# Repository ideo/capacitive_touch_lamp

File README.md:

# Capacitive Touch Lamp
Eagle files and arduino code for the CHIDEO capacitive touch lamp. The surface is separated into nine capacitive touch surfaces. The eight outside surfaces control individual lights, while the center surface turns all lights on.

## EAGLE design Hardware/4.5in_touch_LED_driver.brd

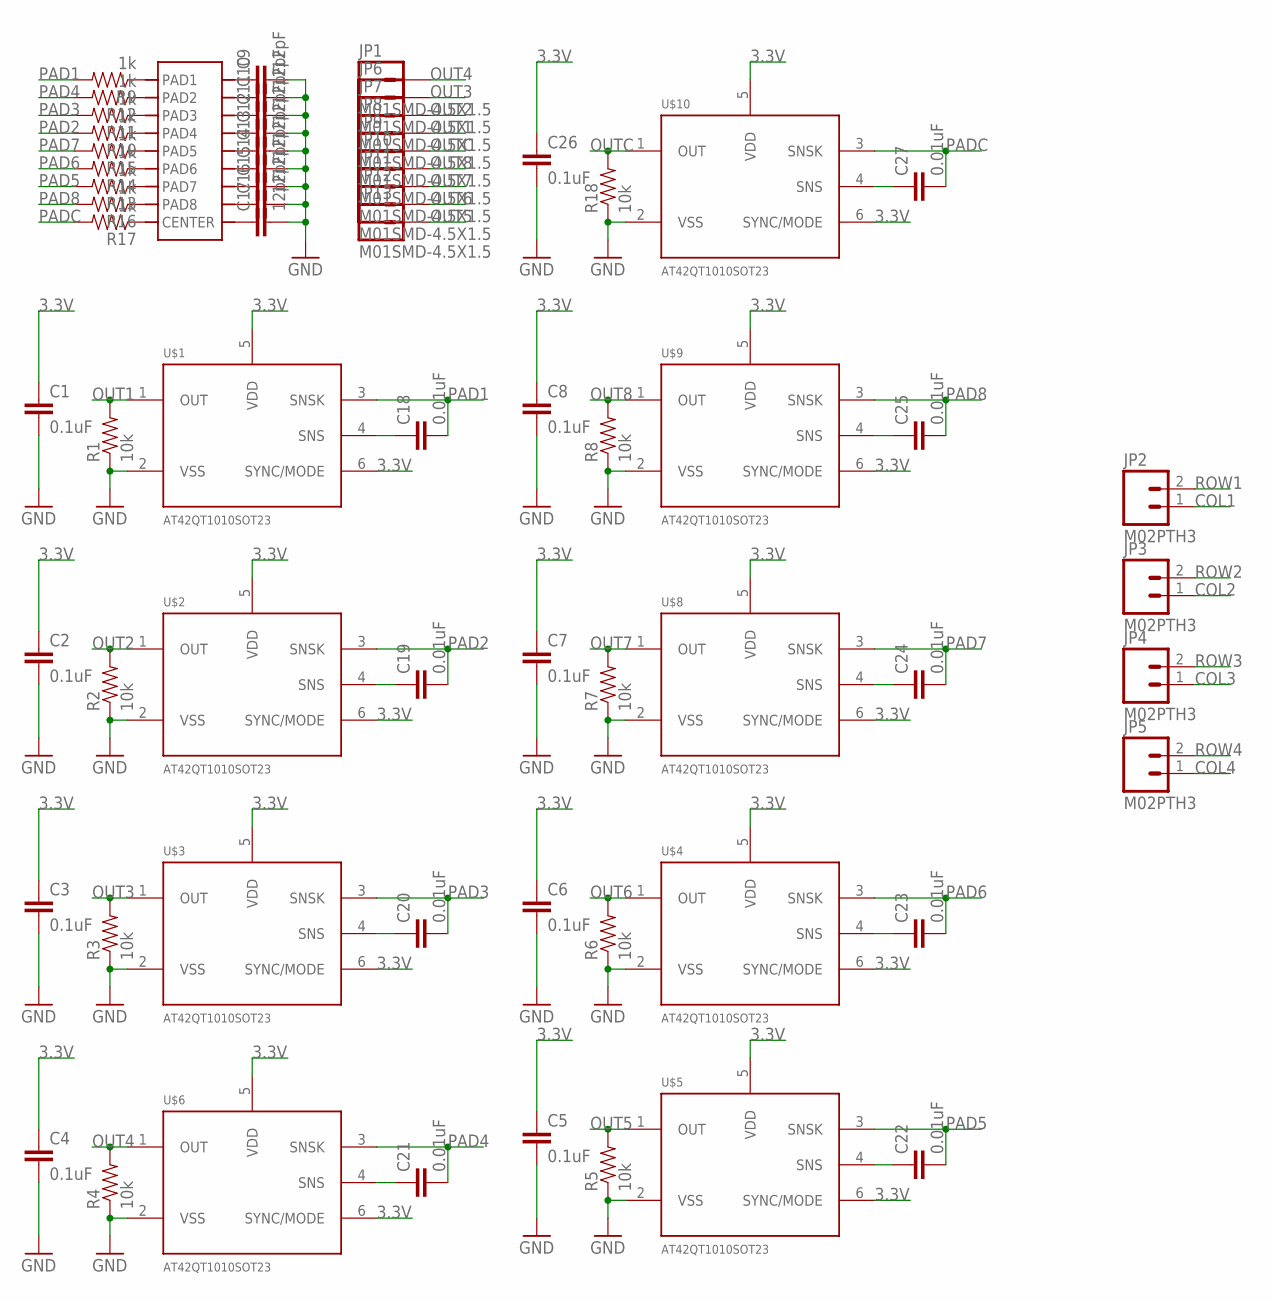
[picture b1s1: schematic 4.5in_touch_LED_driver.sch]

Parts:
C1, C2, C3, C4, C5, C6, C7, C8, C26: 0.1uF; 0603-CAP
C9, C10, C11, C12, C13, C14, C15, C16, C17: 12pF; 0805
C18, C19, C20, C21, C22, C23, C24, C25, C27: 0.01uF; 0805
JP1, JP6, JP7, JP8, JP9, JP10, JP11, JP12, JP13: M01SMD-4.5X1.5; PAD-1.5X4.5
JP2, JP3, JP4, JP5: M02PTH3; 1X02_LONGPADS
R1, R2, R3, R4, R5, R6, R7, R8, R18: 10k; 0603-RES
R9, R10, R11, R12, R13, R14, R15, R16, R17: 1k; 0603-RES
U$1, U$2, U$3, U$4, U$5, U$6, U$8, U$9, U$10: AT42QT1010SOT23; SOT23-6
U$7: 9_PAD_TOUCH4IN; 4IN_TOUCH_PAD

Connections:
3.3V: C1.1, C2.1, C3.1, C4.1, C5.1, C6.1, C7.1, C8.1, C26.1, U$1.5 (VDD), U$1.6 (SYNC/MODE), U$2.5 (VDD), U$2.6 (SYNC/MODE), U$3.5 (VDD), U$3.6 (SYNC/MODE), U$4.5 (VDD), U$4.6 (SYNC/MODE), U$5.5 (VDD), U$5.6 (SYNC/MODE), U$6.5 (VDD), U$6.6 (SYNC/MODE), U$8.5 (VDD), U$8.6 (SYNC/MODE), U$9.5 (VDD), U$9.6 (SYNC/MODE), U$10.5 (VDD), U$10.6 (SYNC/MODE)
COL1: JP2.1
COL2: JP3.1
COL3: JP4.1
COL4: JP5.1
GND: C1.2, C2.2, C3.2, C4.2, C5.2, C6.2, C7.2, C8.2, C9.2, C10.2, C11.2, C12.2, C13.2, C14.2, C15.2, C16.2, C17.2, C26.2, R1.1, R2.1, R3.1, R4.1, R5.1, R6.1, R7.1, R8.1, R18.1, U$1.2 (VSS), U$2.2 (VSS), U$3.2 (VSS), U$4.2 (VSS), U$5.2 (VSS), U$6.2 (VSS), U$8.2 (VSS), U$9.2 (VSS), U$10.2 (VSS)
unnamed: C9.1, U$7.P$10
unnamed: C10.1, U$7.P$11
unnamed: C11.1, U$7.P$12
unnamed: C12.1, U$7.P$13
unnamed: C13.1, U$7.P$14
unnamed: C14.1, U$7.P$15
unnamed: C15.1, U$7.P$16
unnamed: C16.1, U$7.P$17
unnamed: C17.1, U$7.P$18
unnamed: C18.1, U$1.4 (SNS)
unnamed: C27.1, U$10.4 (SNS)
unnamed: R9.1, U$7.P$1 (PAD1)
unnamed: C19.1, U$2.4 (SNS)
unnamed: C20.1, U$3.4 (SNS)
unnamed: R10.1, U$7.P$4 (PAD4)
unnamed: C21.1, U$6.4 (SNS)
unnamed: R11.1, U$7.P$3 (PAD3)
unnamed: C22.1, U$5.4 (SNS)
unnamed: R12.1, U$7.P$2 (PAD2)
unnamed: C23.1, U$4.4 (SNS)
unnamed: R13.1, U$7.P$7 (PAD7)
unnamed: C24.1, U$8.4 (SNS)
unnamed: R14.1, U$7.P$6 (PAD6)
unnamed: C25.1, U$9.4 (SNS)
unnamed: R15.1, U$7.P$5 (PAD5)
unnamed: R16.1, U$7.P$8 (PAD8)
unnamed: R17.1, U$7.P$9 (CENTER)
OUT1: JP8.P$1, R1.2, U$1.1 (OUT)
OUT2: JP7.P$1, R2.2, U$2.1 (OUT)
OUT3: JP6.P$1, R3.2, U$3.1 (OUT)
OUT4: JP1.P$1, R4.2, U$6.1 (OUT)
OUT5: JP13.P$1, R5.2, U$5.1 (OUT)
OUT6: JP12.P$1, R6.2, U$4.1 (OUT)
OUT7: JP11.P$1, R7.2, U$8.1 (OUT)
OUT8: JP10.P$1, R8.2, U$9.1 (OUT)
OUTC: JP9.P$1, R18.2, U$10.1 (OUT)
PAD1: C18.2, R9.2, U$1.3 (SNSK)
PAD2: C19.2, R10.2, U$2.3 (SNSK)
PAD3: C20.2, R11.2, U$3.3 (SNSK)
PAD4: C21.2, R12.2, U$6.3 (SNSK)
PAD5: C22.2, R13.2, U$5.3 (SNSK)
PAD6: C23.2, R14.2, U$4.3 (SNSK)
PAD7: C24.2, R15.2, U$8.3 (SNSK)
PAD8: C25.2, R16.2, U$9.3 (SNSK)
PADC: C27.2, R17.2, U$10.3 (SNSK)
ROW1: JP2.2
ROW2: JP3.2
ROW3: JP4.2
ROW4: JP5.2

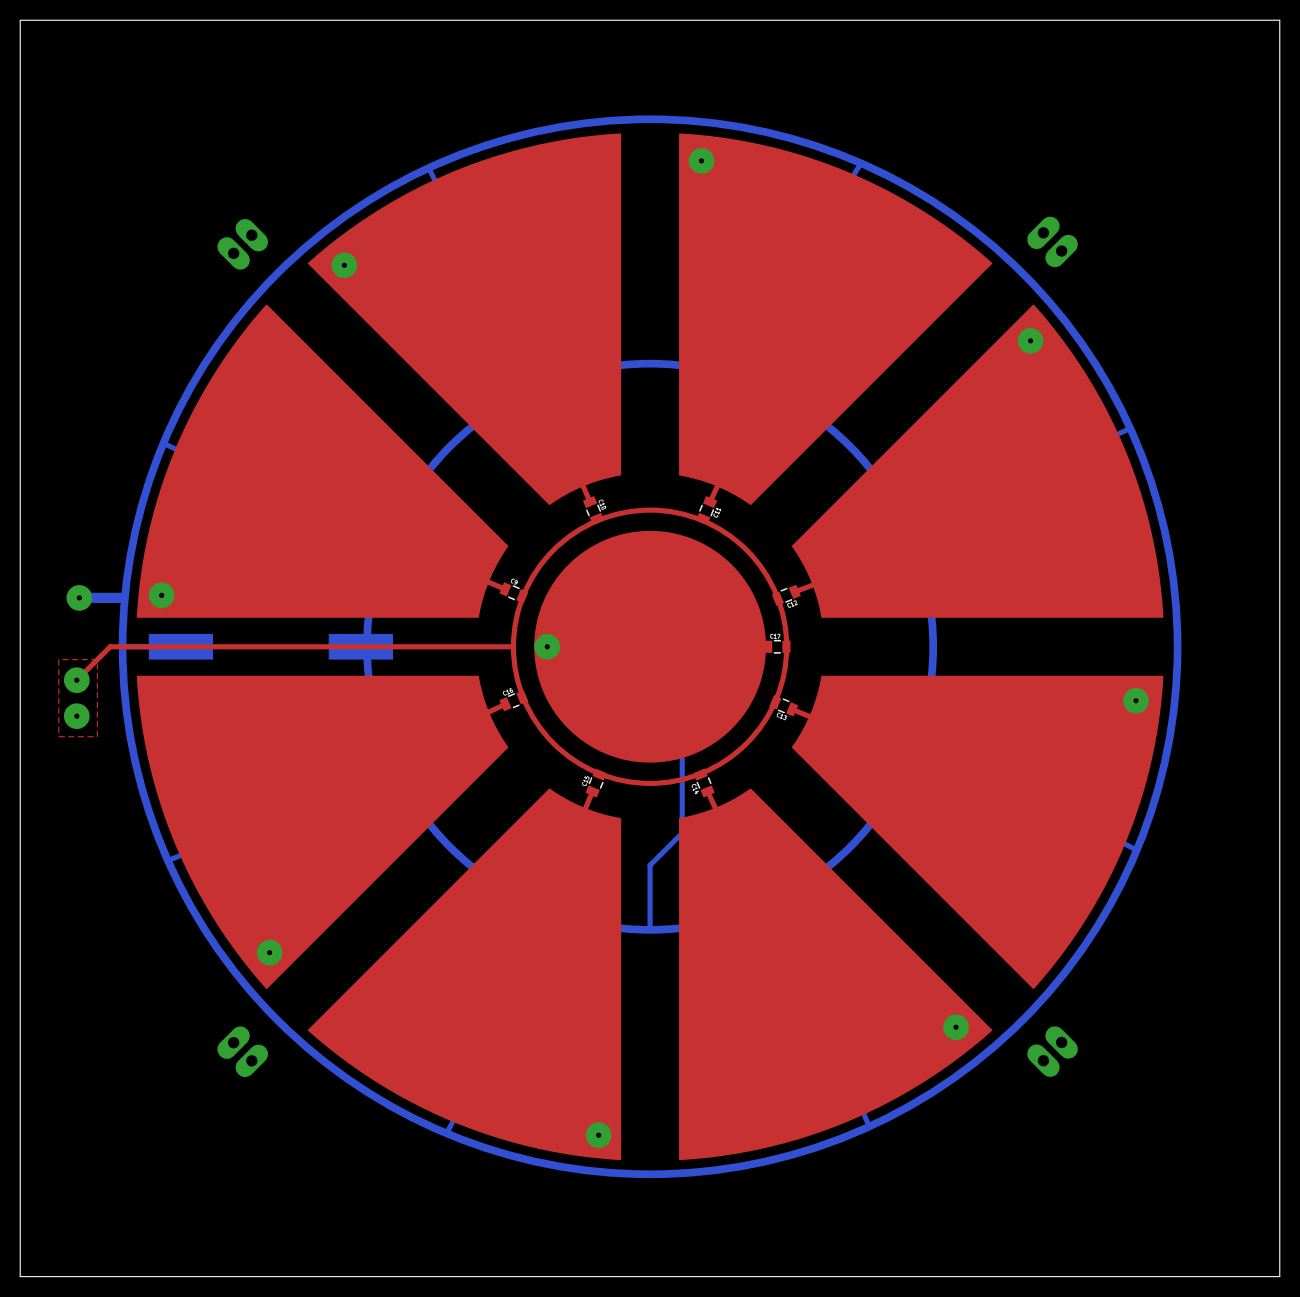
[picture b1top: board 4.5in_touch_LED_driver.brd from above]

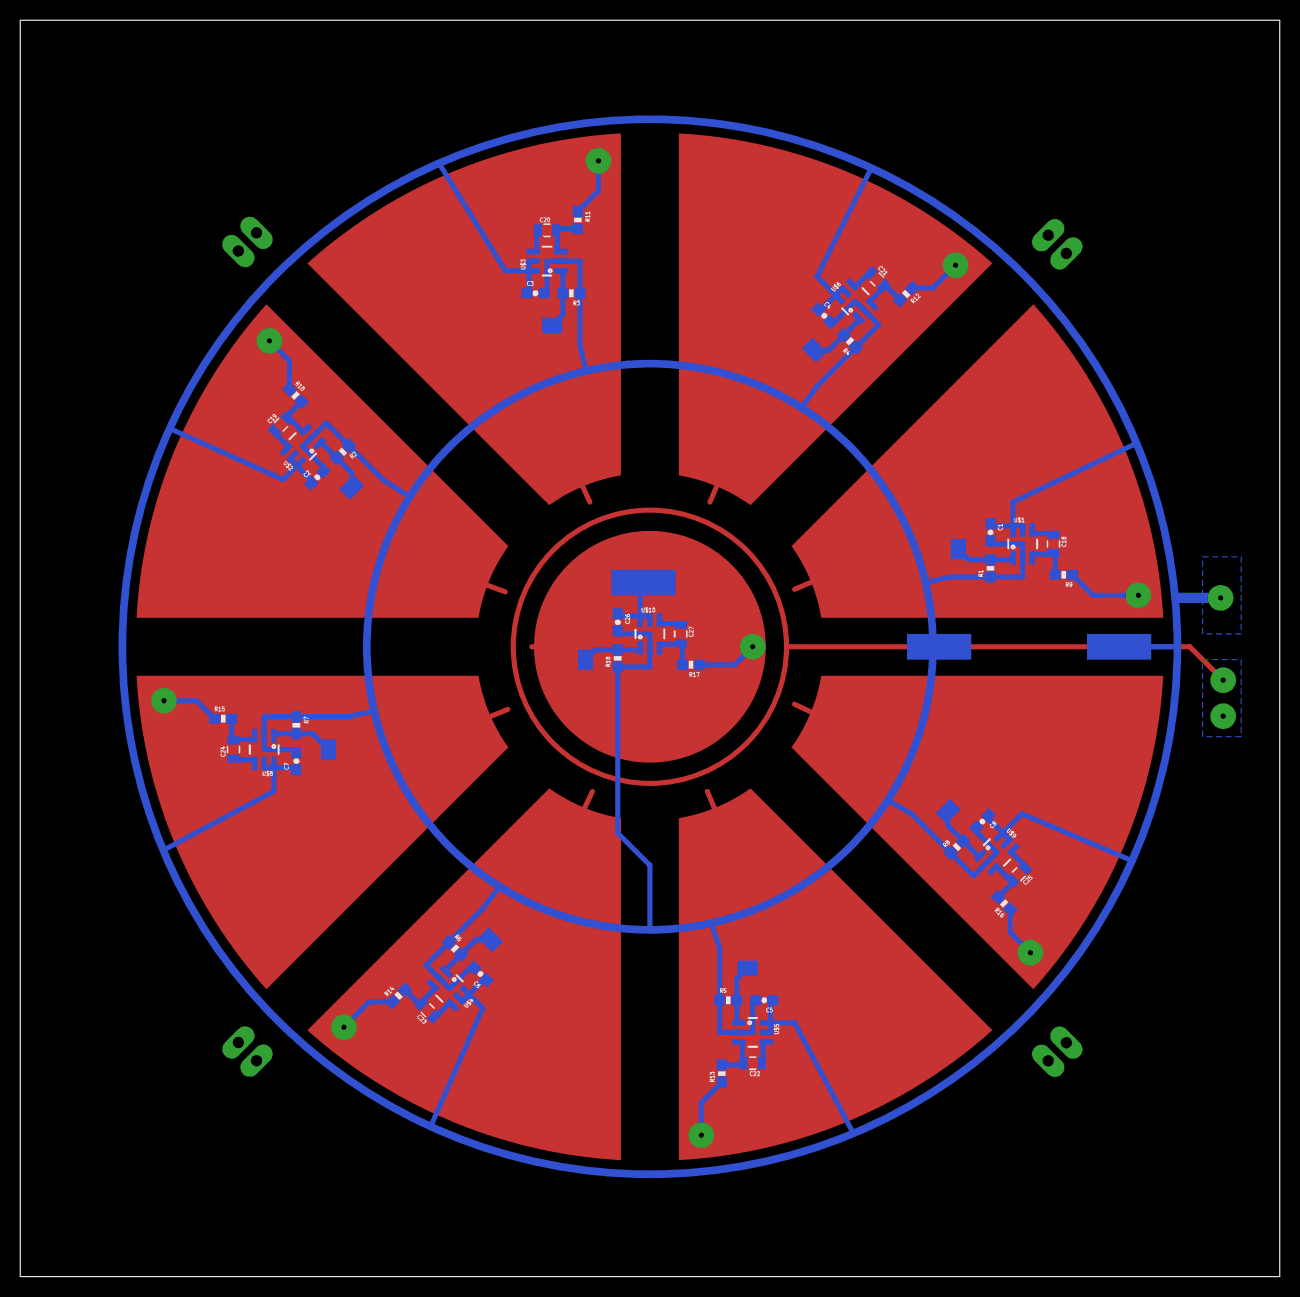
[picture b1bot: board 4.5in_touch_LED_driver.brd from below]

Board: 2 copper layers, 124.4 x 124.1 mm, 68 parts (54 on the bottom side), 47 nets.

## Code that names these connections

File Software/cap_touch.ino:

// https://github.com/wayoda/LedControl
#include "LedControl.h"

// easier to remember inputs as pads, not pin numbers
int PADC = 10;
int PAD1 = 11;
int PAD2 = 12;
int PAD3 = 13;
int PAD4 = 9;
int PAD5 = 8;
int PAD6 = 7;
int PAD7 = 6;
int PAD8 = 5;

// communication lines for MAX72XX
int LCDATA = 2;
int LCLOAD = 3;
int LCCLK = 4;

// LedControl library is used to control MAX727
LedControl lc=LedControl(LCDATA,LCCLK,LCLOAD,1);

void setup() {
  Serial.begin(9600);

  pinMode(PADC, INPUT); // set PADC to input
  pinMode(PAD1, INPUT); // set PAD1 to input
  pinMode(PAD2, INPUT); // set PAD2 to input
  pinMode(PAD3, INPUT); // set PAD3 to input
  pinMode(PAD4, INPUT); // set PAD3 to input
  pinMode(PAD5, INPUT); // set PAD3 to input
  pinMode(PAD6, INPUT); // set PAD3 to input
  pinMode(PAD7, INPUT); // set PAD3 to input
  pinMode(PAD8, INPUT); // set PAD3 to input

  /*
   The MAX72XX is in power-saving mode on startup,
   we have to do a wakeup call
   */
  lc.shutdown(0,false);
  /* Set the brightness to a medium values */
  lc.setIntensity(0,15);
  /* and clear the display */
  lc.clearDisplay(0);
}

void loop() {
  // MAX72XX accepts binary LED controls, so only add LEDs to turn on
  byte row0 = B00000000;
  byte row1 = B00000000;
  byte row2 = B00000000;
  byte row3 = B00000000;

  // listen for any capacitive touch events and control LEDs accordingly
  if (digitalRead(PADC)) {
    row0 = B11110000;
    row1 = B11110000;
    row2 = B11110000;
    row3 = B11110000;
  }
  if (digitalRead(PAD1)) {
    row2 += B11000000;
  }
  if (digitalRead(PAD2)) {
    row2 += B00110000;
  }
  if (digitalRead(PAD3)) {
    row3 += B00110000;
  }
  if (digitalRead(PAD4)) {
    row3 += B11000000;
  }
  if (digitalRead(PAD5)) {
    row1 += B00110000;
  }
  if (digitalRead(PAD6)) {
    row1 += B11000000;
  }
  if (digitalRead(PAD7)) {
    row0 += B11000000;
  }
  if (digitalRead(PAD8)) {
    row0 += B00110000;
  }

  // turn LEDs on or off depending on what's touched
  lc.setRow(0,0,row0);
  lc.setRow(0,1,row1);
  lc.setRow(0,2,row2);
  lc.setRow(0,3,row3);
}

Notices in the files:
parts and their libraries:
SparkFun-Capacitors: Licensing: Creative Commons ShareAlike 4.0 International - https://creativecommons.org/licenses/by-sa/4.0
